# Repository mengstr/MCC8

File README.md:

# MCC8

This is a small handheld PIC24-based CHIP-8 emulator game console. A cheap Noika 1202 LCD is used as the display and a CR123A 3 volt lithium battery for power. More info about the project can be found at [DangerousPrototypes.com](http://dangerousprototypes.com/forum/viewtopic.php?f=56&t=6018)

The sixteen buttons on the right is a hexadecimal keypad arranged in the same strange order as the COSMAC had for maximum keyplacement compability. Then I've added four extra buttons to go into game selection menu mode and other stuffs for future use. 

Read more about CHIP-8 at [Wikipedia](http://en.wikipedia.org/wiki/CHIP-8)

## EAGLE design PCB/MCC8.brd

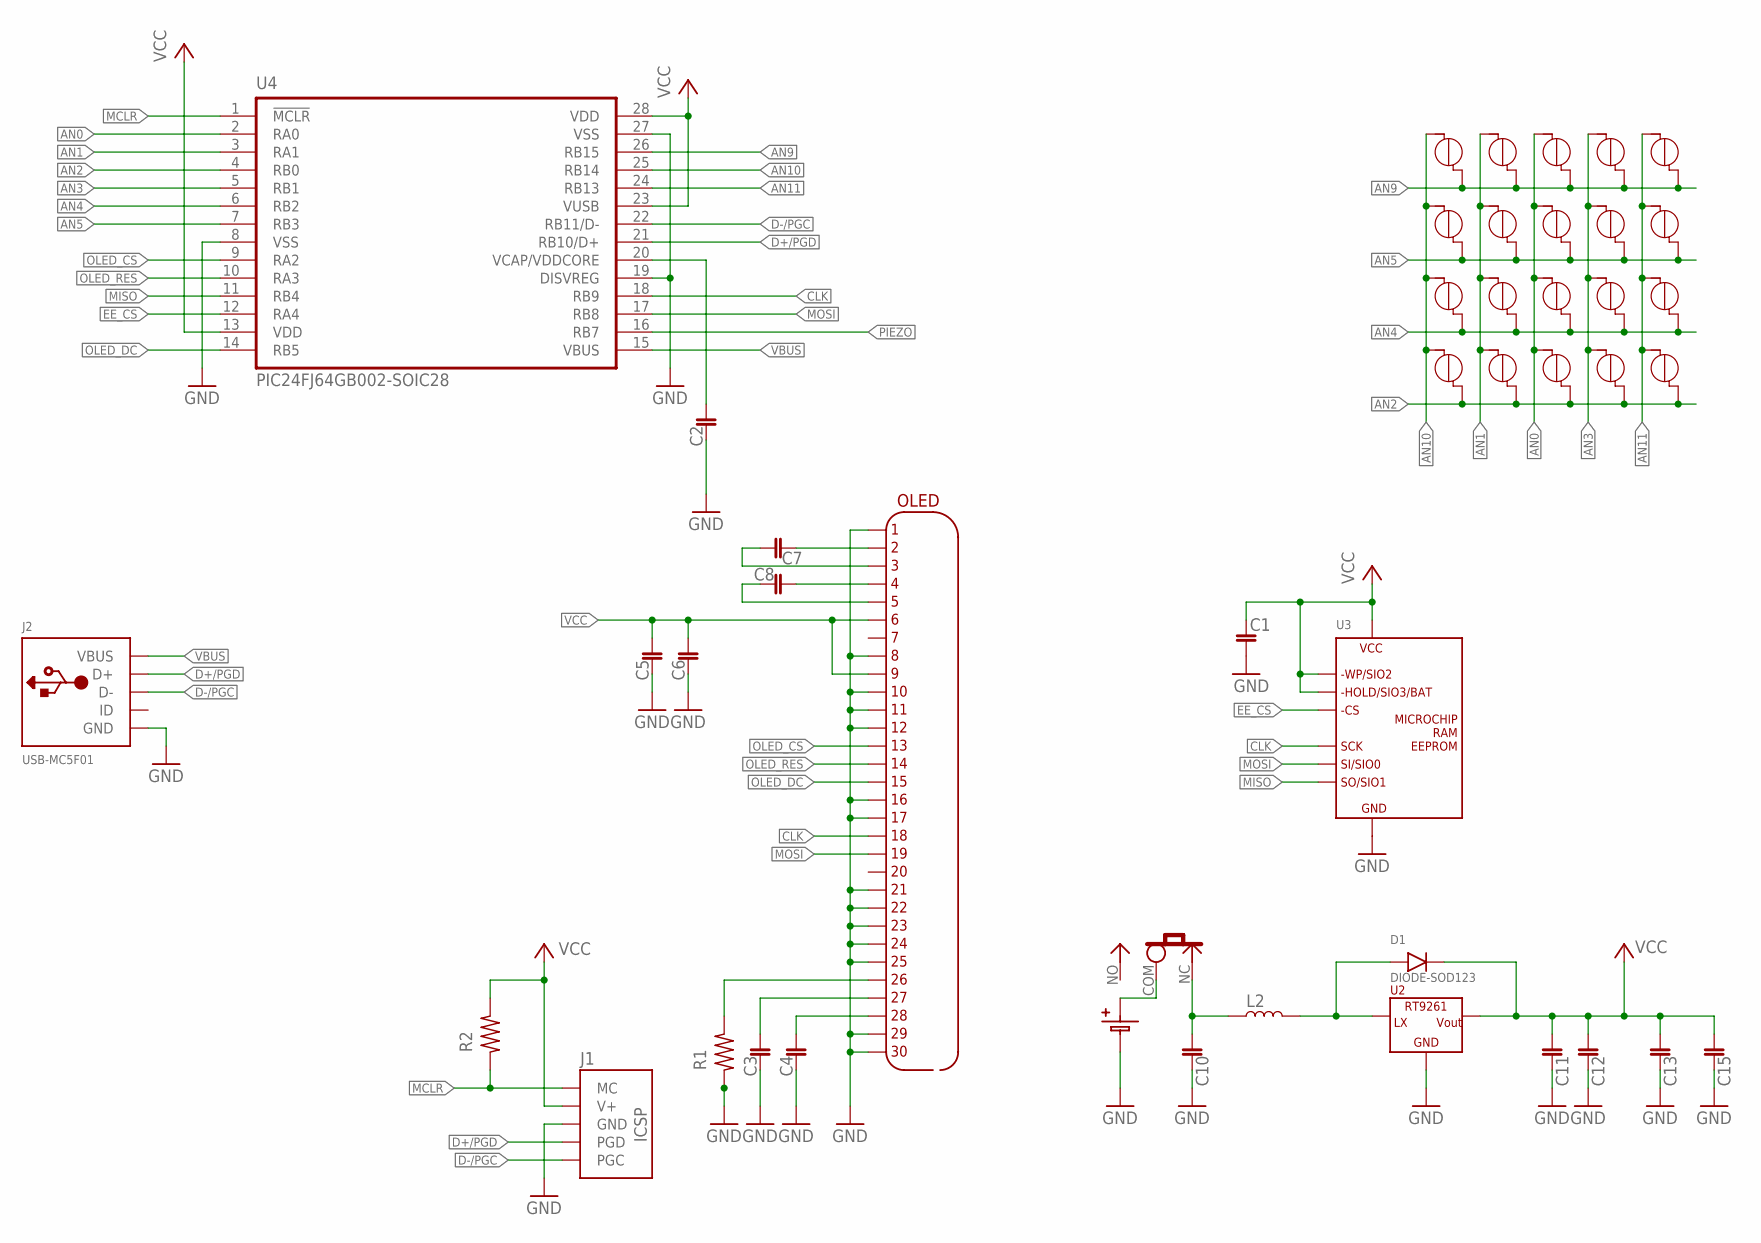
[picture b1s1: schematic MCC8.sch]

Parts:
B1, B2, B3, B4, B5, B6, B7, B8, B9, B10, B11, B12, B13, B14, B15, B16, B17, B18, B19, B20: TOUCH-CAP2-7; TOUCH-CAP2-7MM
BA2: BATTERY2-AAA1; BAT-AAA1
C1, C2, C3, C4, C5, C6, C7, C8, C10, C11, C12, C13, C15: C-0805; C0805
D1: DIODE-SOD123; SOD123
J1: ICSP-SMD-B
J2: USB-MC5F01; USB-MICRO-MC5F01
L2: L-BOURNS-SRP7030; IND-BOURNS-SRP7030
R1, R2: R-0805; R0805
SW1: SLIDE1-PCM12; SW-PCM12
U2: RT9261-SOT89; SOT89
U3: MICROCHIP-SERIALMEM8; SO08
U4: PIC24FJ64GB002-SOIC28; SO28W
U$2: OLED30-A; OLED128X64

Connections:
AN0: B9.P$1, B10.P$1, B11.P$1, B12.P$1, U4.2 (RA0)
AN1: B5.P$1, B6.P$1, B7.P$1, B8.P$1, U4.3 (RA1)
AN2: B4.P$2, B8.P$2, B12.P$2, B16.P$2, B20.P$2, U4.4 (RB0)
AN3: B13.P$1, B14.P$1, B15.P$1, B16.P$1, U4.5 (RB1)
AN4: B3.P$2, B7.P$2, B11.P$2, B15.P$2, B19.P$2, U4.6 (RB2)
AN5: B2.P$2, B6.P$2, B10.P$2, B14.P$2, B18.P$2, U4.7 (RB3)
AN9: B1.P$2, B5.P$2, B9.P$2, B13.P$2, B17.P$2, U4.26 (RB15)
AN10: B1.P$1, B2.P$1, B3.P$1, B4.P$1, U4.25 (RB14)
AN11: B17.P$1, B18.P$1, B19.P$1, B20.P$1, U4.24 (RB13)
BAT: BA2.PLUS (POS1), SW1.COM
BAT-SWITCHED: C10.1, L2.P$1, SW1.NC
CLK: U3.6 (SCK), U4.18 (RB9), U$2.P$18
D+/PGD: J1.PGD, J2.P3 (D+), U4.21 (RB10/D+)
D-/PGC: J1.PGC, J2.P2 (D-), U4.22 (RB11/D-)
EE_CS: U3.1 (CS), U4.12 (RA4)
GND: BA2.MINUS (NEG), C1.2, C2.2, C3.2, C4.2, C5.2, C6.2, C10.2, C11.2, C12.2, C13.2, C15.2, J1.GND, J2.P5 (GND), R1.1, U2.1 (GND), U3.4 (GROUND), U4.8 (VSS), U4.19 (DISVREG), U4.27 (VSS), U$2.P$1, U$2.P$8, U$2.P$10, U$2.P$11, U$2.P$12, U$2.P$16, U$2.P$17, U$2.P$21, U$2.P$22, U$2.P$23, U$2.P$24, U$2.P$25, U$2.P$29, U$2.P$30
LX: D1.A, L2.P$2, U2.3 (LX)
MCLR: J1.VPP (MC), R2.1, U4.1 (!MCLR)
MISO: U3.2 (SO), U4.11 (RB4)
MOSI: U3.5 (SI), U4.17 (RB8), U$2.P$19
unnamed: C4.1, U$2.P$28
unnamed: C3.1, U$2.P$27
unnamed: R1.2, U$2.P$26
unnamed: C7.2, U$2.P$2
unnamed: C7.1, U$2.P$3
unnamed: C8.1, U$2.P$4
unnamed: C8.2, U$2.P$5
OLED_CS: U4.9 (RA2), U$2.P$13
OLED_DC: U4.14 (RB5), U$2.P$15
OLED_RES: U4.10 (RA3), U$2.P$14
PIEZO: U4.16 (RB7)
VBUS: J2.P1 (VBUS), U4.15 (VBUS)
VCC: C1.1, C5.1, C6.1, C11.1, C12.1, C13.1, C15.1, D1.C, J1.V+, R2.2, U2.2 (VOUT), U2.2@1 (VOUT), U3.3 (WP), U3.7 (HOLD), U3.8 (POW), U4.13 (VDD), U4.23 (VUSB), U4.28 (VDD), U$2.P$6, U$2.P$9
VDDCORE: C2.1, U4.20 (VCAP/VDDCORE)

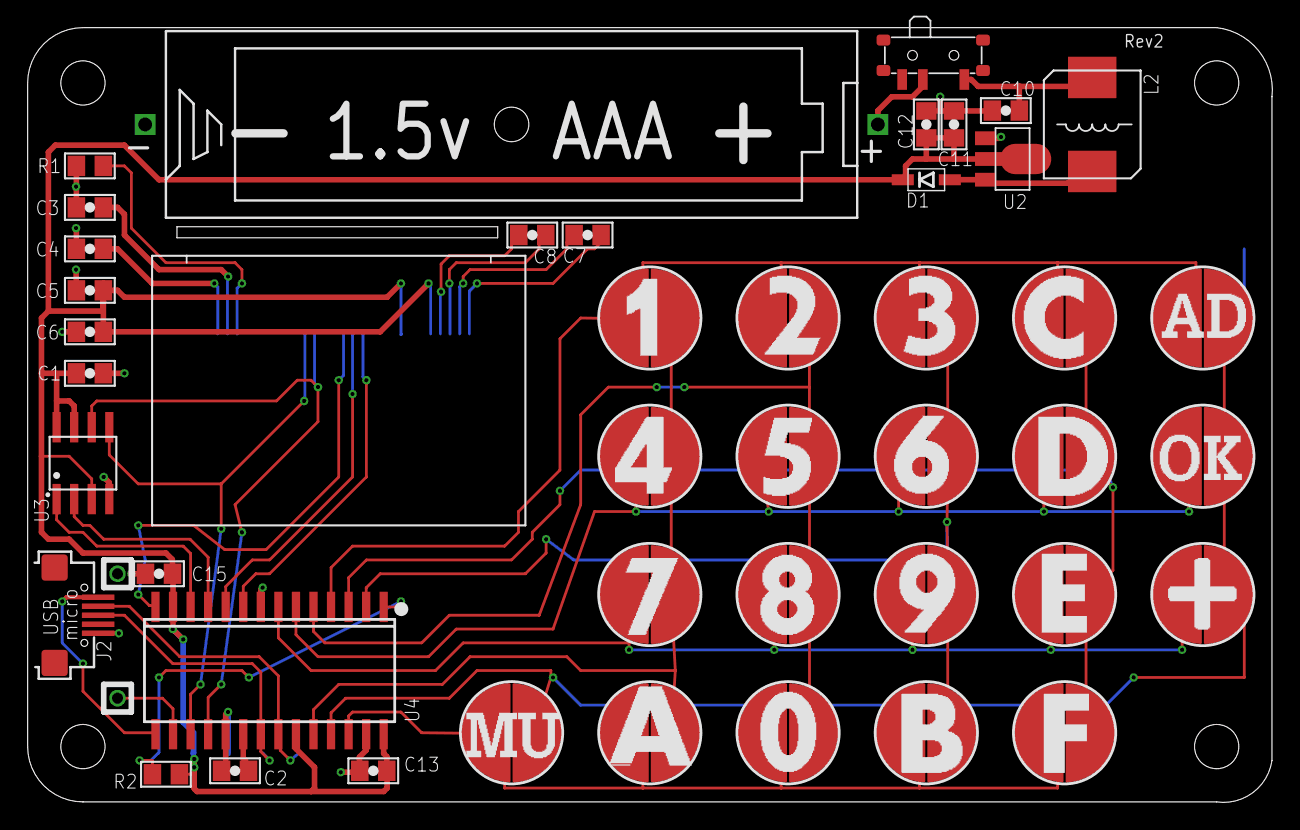
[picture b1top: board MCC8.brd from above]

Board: 2 copper layers, 90.0 x 56.0 mm, 45 parts (1 on the bottom side), 33 nets.

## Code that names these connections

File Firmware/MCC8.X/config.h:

#ifndef CONFIG_H_
#define	CONFIG_H_

#include <stdlib.h>
#include <stdint.h>
#include <xc.h>

#define _XTAL_FREQ (8000000ULL)
#define FCY (_XTAL_FREQ/2)

extern void __delay32(unsigned long cycles);

#define __delay_ms(d) \
  { __delay32( (unsigned long) (((unsigned long long) d)*(FCY)/1000ULL)); }


#define __delay_us(d) \
  { __delay32( (unsigned long) (((unsigned long long) d)*(FCY)/1000000ULL)); }

#define  testbit(var, bit)   ((var) & (1UL <<(bit)))
#define  setbit(var, bit)    ((var) |= (1UL << (bit)))
#define  clrbit(var, bit)    ((var) &= ~(1UL << (bit)))


#define OLED_DC_TRIS    TRISBbits.TRISB5
#define OLED_CS_TRIS    TRISAbits.TRISA2
#define OLED_RES_TRIS   TRISAbits.TRISA3
#define EE_CS_TRIS      TRISAbits.TRISA4
#define PIEZO_TRIS      TRISBbits.TRISB7

#define OLED_DC         LATBbits.LATB5
#define OLED_CS         LATAbits.LATA2
#define OLED_RES        LATAbits.LATA3
#define EE_CS           LATAbits.LATA4
#define PIEZO           LATBbits.LATB7

#define TOUCH0_TRIS     TRISAbits.TRISA0
#define TOUCH1_TRIS     TRISAbits.TRISA1
#define TOUCH2_TRIS     TRISBbits.TRISB0
#define TOUCH3_TRIS     TRISBbits.TRISB1
#define TOUCH4_TRIS     TRISBbits.TRISB2
#define TOUCH5_TRIS     TRISBbits.TRISB3
#define TOUCH6_TRIS     TRISBbits.TRISB15
#define TOUCH7_TRIS     TRISBbits.TRISB14
#define TOUCH8_TRIS     TRISBbits.TRISB13

#define TOUCH0          LATAbits.LATA0
#define TOUCH1          LATAbits.LATA1
#define TOUCH2          LATBbits.LATB0
#define TOUCH3          LATBbits.LATB1
#define TOUCH4          LATBbits.LATB2
#define TOUCH5          LATBbits.LATB3
#define TOUCH6          LATBbits.LATB15
#define TOUCH7          LATBbits.LATB14
#define TOUCH8          LATBbits.LATB13

#endif

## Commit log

2013-11-22 PCB Rev1
2013-11-22 Basic Firmware
2013-11-22 Added KeyWaitForRelease()
2013-11-22 Moved LCD_D LCD_C from source to header
2013-11-22 Broke out emulation in main.c to chip8.c
2013-11-22 Added array of game lengths
2013-11-22 c8st and c8dt is now handled by 60 Hz timer1 interrupt
2013-11-22 Image of PCB
2013-11-22 Updated README.md with some real content
2014-11-05 MCC8 OLED version
2014-11-05 Gerbers & Eagle for last version of LCD
2014-11-05 Eagle files for OLED
2014-11-05 Gebers for OLED version
2014-11-05 Consolidated games into into a struct
